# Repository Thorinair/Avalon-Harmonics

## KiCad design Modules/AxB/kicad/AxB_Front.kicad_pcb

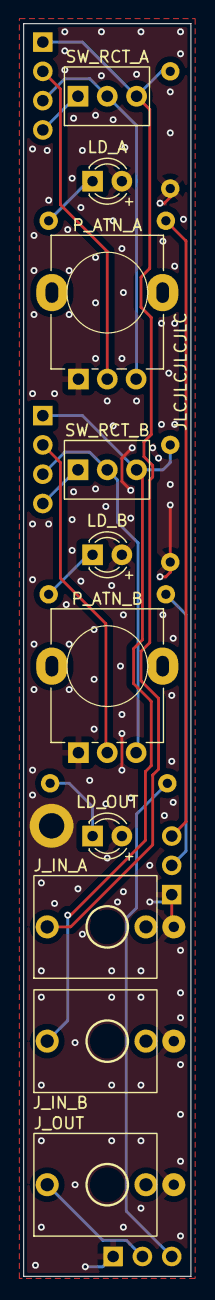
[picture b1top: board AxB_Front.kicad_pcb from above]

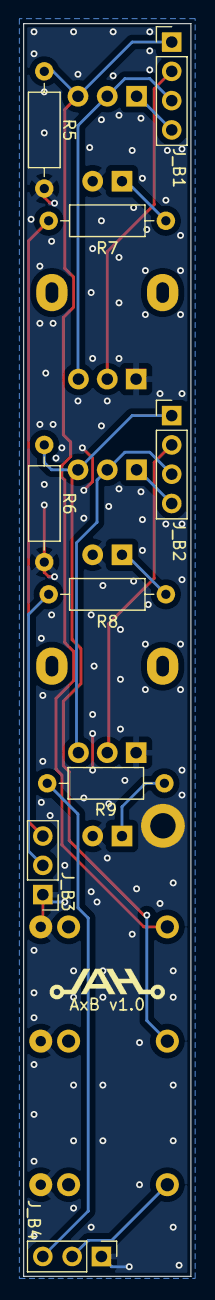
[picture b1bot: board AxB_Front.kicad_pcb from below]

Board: 2 copper layers, 14.5 x 108.6 mm, 19 parts (9 on the bottom side), 16 nets.

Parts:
J_B1, J_B2: Conn_01x04_Female; PinHeader_1x04_P2.54mm_Vertical
J_B3, J_B4: Conn_01x03_Female; PinHeader_1x03_P2.54mm_Vertical
J_IN_A: PJ301M-12
J_IN_B: PJ301M-12
J_OUT: PJ301M-12
LD_A: LED (Bi); LED_D3.0mm_FlatTop
LD_B: LED (Bi); LED_D3.0mm_FlatTop
LD_OUT: LED (Bi); LED_D3.0mm_FlatTop
P_ATN_A: B50k; Potentiometer Alpha RD901F-40-00D
P_ATN_B: B50k; Potentiometer Alpha RD901F-40-00D
R5, R6: 100k; R_Axial_DIN0207_L6.3mm_D2.5mm_P10.16mm_Horizontal
R7, R8, R9: 1k; R_Axial_DIN0207_L6.3mm_D2.5mm_P10.16mm_Horizontal
SW_RCT_A: SW_SPDT; SPDT
SW_RCT_B: SW_SPDT; SPDT

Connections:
GND: J_B3.1, J_B4.1, J_IN_A.GND, J_IN_B.GND, J_OUT.GND, LD_A.2 (A), LD_B.2 (A), LD_OUT.2 (A), P_ATN_A.1, P_ATN_B.1, R5.1, R6.1
unnamed: J_B1.1, J_IN_A.SIG, R5.2, SW_RCT_A.3 (C)
unnamed: J_B1.2, P_ATN_A.2
unnamed: J_B1.3, P_ATN_A.3, SW_RCT_A.2 (B)
unnamed: J_B1.4, SW_RCT_A.1 (A)
unnamed: J_B2.1, J_IN_B.SIG, R6.2, SW_RCT_B.3 (C)
unnamed: J_B2.2, P_ATN_B.2
unnamed: J_B2.3, P_ATN_B.3, SW_RCT_B.2 (B)
unnamed: J_B2.4, SW_RCT_B.1 (A)
unnamed: J_B3.2, R8.2
unnamed: J_B3.3, R7.2
unnamed: J_B4.2, J_OUT.SIG
unnamed: J_B4.3, R9.2
unnamed: LD_A.1 (K), R7.1
unnamed: LD_B.1 (K), R8.1
unnamed: LD_OUT.1 (K), R9.1

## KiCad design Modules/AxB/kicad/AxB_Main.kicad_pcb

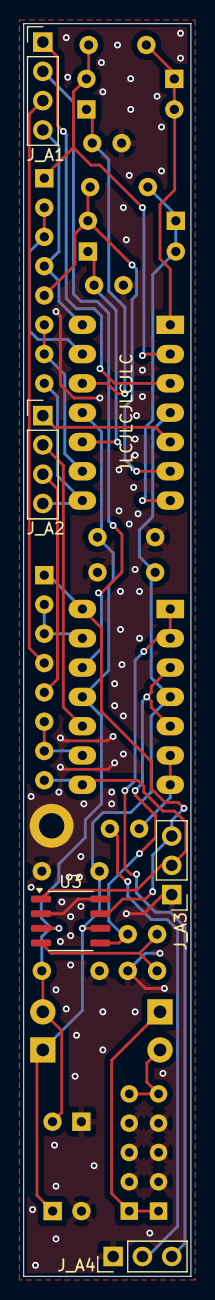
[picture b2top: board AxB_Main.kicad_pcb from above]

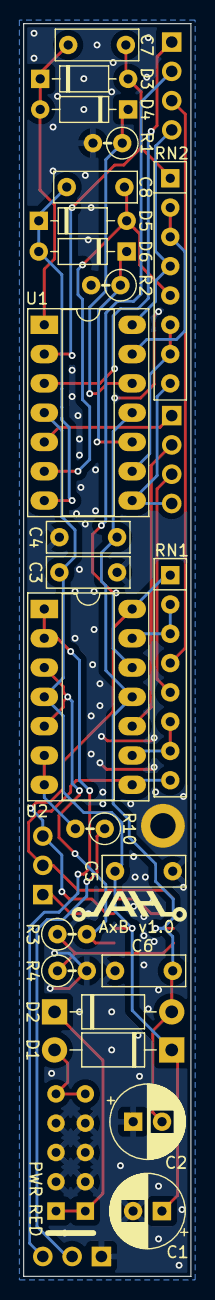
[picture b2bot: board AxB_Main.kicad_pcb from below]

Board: 2 copper layers, 14.5 x 108.6 mm, 29 parts (24 on the bottom side), 30 nets.

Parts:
C1, C2: 47uF; CP_Radial_D6.3mm_P2.50mm
C3, C4, C5, C6: 0.1uF; C_Disc_D7.0mm_W2.5mm_P5.00mm
C7, C8: 47pF; C_Disc_D7.0mm_W2.5mm_P5.00mm
D1, D2: 1N4001; D_DO-41_SOD81_P10.16mm_Horizontal
D3, D4, D5, D6: 1N4148; D_DO-35_SOD27_P7.62mm_Horizontal
J_A1, J_A2: Conn_01x04_Male; PinHeader_1x04_P2.54mm_Vertical
J_A3, J_A4: Conn_01x03_Male; PinHeader_1x03_P2.54mm_Vertical
PWR1: PWR_10_Pin; Eurorack Power 10 Pin
R1, R2: 10k; R_Axial_DIN0207_L6.3mm_D2.5mm_P2.54mm_Vertical
R3: 33k; R_Axial_DIN0207_L6.3mm_D2.5mm_P2.54mm_Vertical
R4: 100k; R_Axial_DIN0207_L6.3mm_D2.5mm_P2.54mm_Vertical
R10: 1k; R_Axial_DIN0207_L6.3mm_D2.5mm_P2.54mm_Vertical
RN1: 100k; R_Array_SIP8
RN2: 10k; R_Array_SIP8
U1, U2: TL074; DIP-14_W7.62mm_Socket_LongPads
U3: AD633JR; SO-8_3.9x4.9mm_P1.27mm

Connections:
+12V: C1.1, C3.1, C5.2, D1.1 (K), U1.4 (V+), U2.4 (V+), U3.6 (+V_{S})
-12V: C2.2, C4.2, C6.2, D2.2 (A), U1.11 (V-), U2.11 (V-), U3.3 (-V_{S})
/AXB: R3.2, U2.3 (+), U2.5 (+), U3.5 (W)
/IN_A: J_A1.1, U1.3 (+)
/IN_B: J_A2.1, U1.5 (+)
/LED_A: J_A3.3, RN1.1 (R1.1), U2.14, U3.7 (X1)
/LED_B: J_A3.2, RN1.8 (R4.2), U2.8, U3.1 (Y1)
/LED_OUT: J_A4.3, U2.1, U2.2 (-)
/OUT: J_A4.2, R10.1
/RECT_A: J_A1.4, RN2.4 (R2.2), U1.14
/RECT_B: J_A2.4, RN2.8 (R4.2), U1.8
GND: C1.2, C2.1, C3.2, C4.1, C5.1, C6.1, J_A3.1, J_A4.1, PWR1.2 (GND), R1.2, R2.2, R4.2, U3.2 (Y2), U3.8 (X2)
unnamed: D1.2 (A), PWR1.1 (+12V)
unnamed: D2.1 (K), PWR1.3 (-12V)
unnamed: C7.1, D3.2 (A), RN2.1 (R1.1), U1.2 (-)
unnamed: C7.2, D3.1 (K), D4.2 (A), U1.1
unnamed: D4.1 (K), R1.1, U1.12 (+)
unnamed: C8.1, D5.2 (A), RN2.5 (R3.1), U1.6 (-)
unnamed: C8.2, D5.1 (K), D6.2 (A), U1.7
unnamed: D6.1 (K), R2.1, U1.10 (+)
unnamed: J_A1.2, U2.12 (+)
unnamed: J_A1.3, RN1.4 (R2.2)
unnamed: J_A2.2, U2.10 (+)
unnamed: J_A2.3, RN1.5 (R3.1)
unnamed: RN1.2 (R1.2), RN1.3 (R2.1), U2.13 (-)
unnamed: RN1.6 (R3.2), RN1.7 (R4.1), U2.9 (-)
unnamed: RN2.2 (R1.2), RN2.3 (R2.1), U1.13 (-)
unnamed: RN2.6 (R3.2), RN2.7 (R4.1), U1.9 (-)
unnamed: R10.2, U2.6 (-), U2.7
unnamed: R3.1, R4.1, U3.4 (Z)

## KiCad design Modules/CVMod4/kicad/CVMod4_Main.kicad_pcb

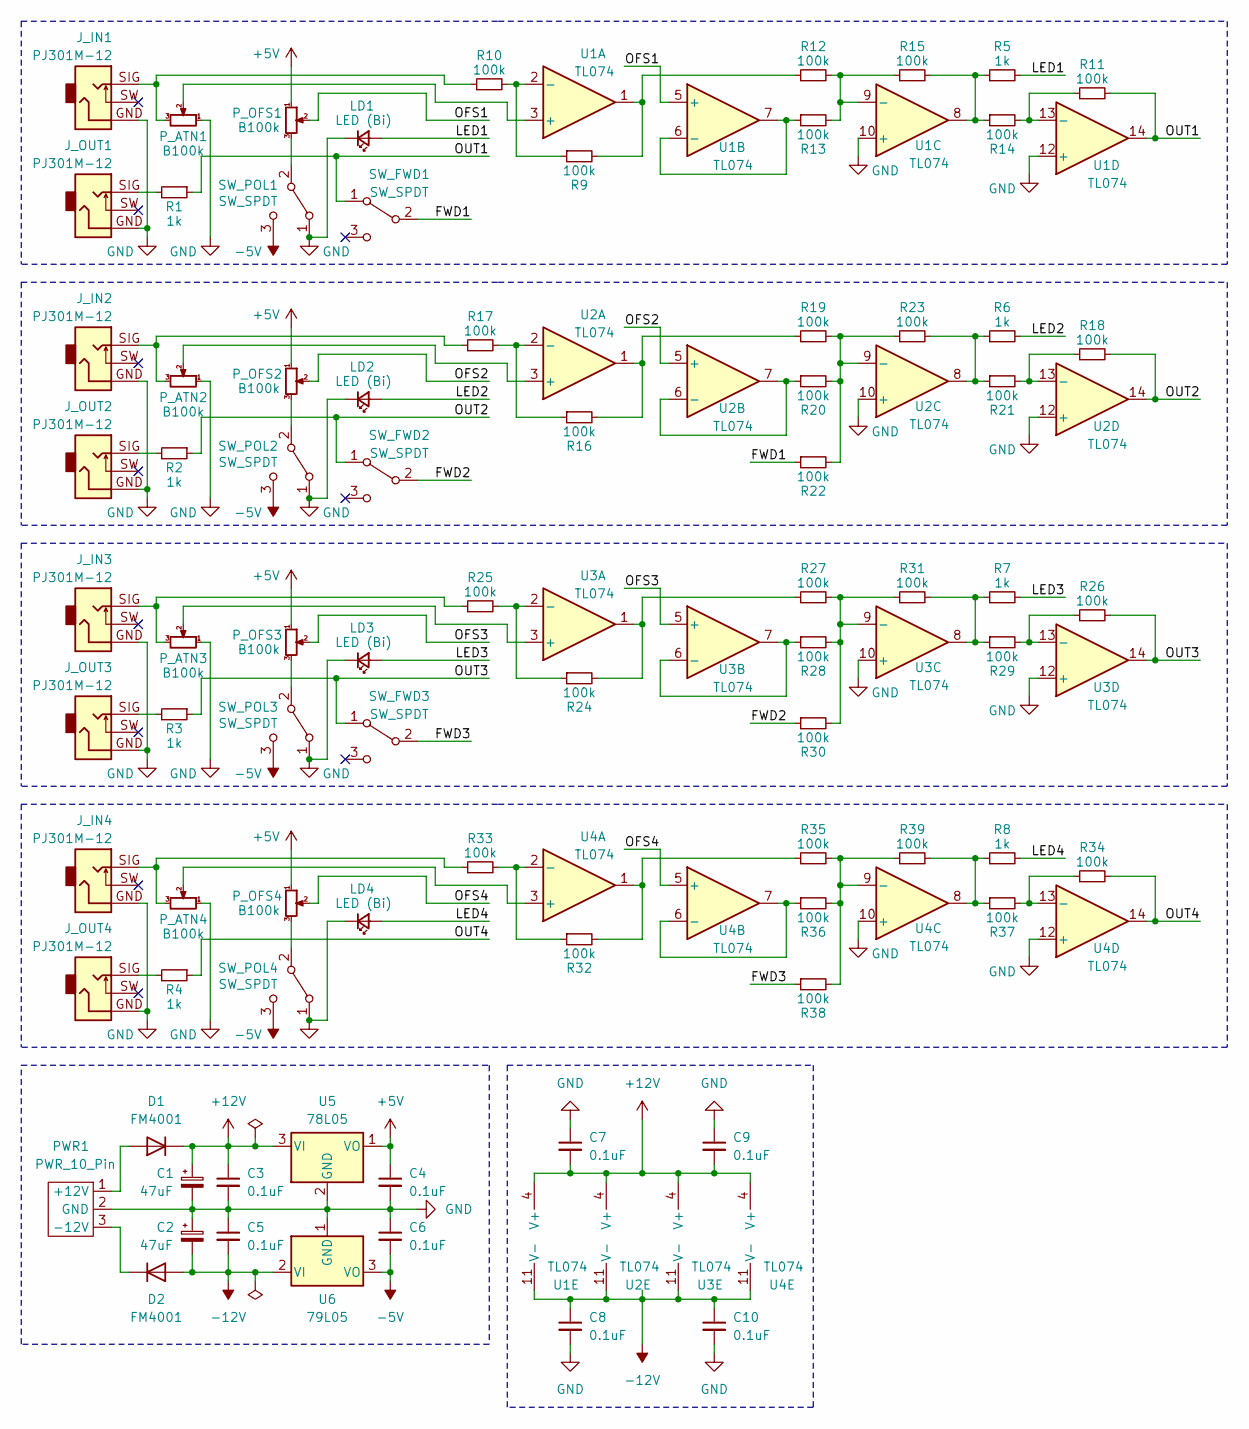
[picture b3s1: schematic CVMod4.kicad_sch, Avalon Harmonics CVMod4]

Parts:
C1, C2: 47uF; CP_Elec_6.3x5.3
C3, C4, C5, C6, C7, C8, C9, C10: 0.1uF; C_0603_1608Metric_Pad1.08x0.95mm_HandSolder
D1, D2: FM4001; D_SOD-123F_AH
J_IN1, J_IN2, J_IN3, J_IN4: PJ301M-12; PJ301M-12 Offset
J_OUT1, J_OUT2, J_OUT3, J_OUT4: PJ301M-12; PJ301M-12 Offset
LD1, LD2, LD3, LD4: LED (Bi); LED_D3.0mm_FlatTop
PWR1: PWR_10_Pin; Eurorack Power 10 Pin
P_ATN1, P_ATN2, P_ATN3, P_ATN4: B100k; Potentiometer Song Huei 9mm Trimmer
P_OFS1, P_OFS2, P_OFS3, P_OFS4: B100k; Potentiometer_Bourns_PTA3043_Single_Slide
R1, R2, R3, R4, R5, R6, R7, R8: 1k; R_0603_1608Metric_Pad0.98x0.95mm_HandSolder
R9, R10, R11, R12, R13, R14, R15, R16, R17, R18, R19, R20, R21, R22, R23, R24, R25, R26, R27, R28, R29, R30, R31, R32, R33, R34, R35, R36, R37, R38, R39: 100k; R_0603_1608Metric_Pad0.98x0.95mm_HandSolder
SW_FWD1, SW_FWD2, SW_FWD3: SW_SPDT; SPDT
SW_POL1, SW_POL2, SW_POL3, SW_POL4: SW_SPDT; SPDT
U1, U2, U3, U4: TL074; SO-14_3.9x8.65mm_P1.27mm_AH
U5: 78L05; SOT-89-3_Handsoldering
U6: 79L05; SOT-89-3_Handsoldering

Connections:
+5V: C4.1, P_OFS1.1, P_OFS2.1, P_OFS3.1, P_OFS4.1, U5.1 (VO)
+12V: C1.1, C3.1, C7.2, C9.2, D1.1 (K), U1.4 (V+), U2.4 (V+), U3.4 (V+), U4.4 (V+), U5.3 (VI)
-5V: C6.2, SW_POL1.3 (C), SW_POL2.3 (C), SW_POL3.3 (C), SW_POL4.3 (C), U6.3 (VO)
-12V: C2.2, C5.2, C8.1, C10.1, D2.2 (A), U1.11 (V-), U2.11 (V-), U3.11 (V-), U4.11 (V-), U6.2 (VI)
/FWD1: R22.1, SW_FWD1.2 (B)
/FWD2: R30.1, SW_FWD2.2 (B)
/FWD3: R38.1, SW_FWD3.2 (B)
/LED1: LD1.2 (A), R5.2
/LED2: LD2.2 (A), R6.2
/LED3: LD3.2 (A), R7.2
/LED4: LD4.2 (A), R8.2
/OFS1: P_OFS1.2, U1.5 (+)
/OFS2: P_OFS2.2, U2.5 (+)
/OFS3: P_OFS3.2, U3.5 (+)
/OFS4: P_OFS4.2, U4.5 (+)
/OUT1: R1.1, R11.2, SW_FWD1.1 (A), U1.14
/OUT2: R2.1, R18.2, SW_FWD2.1 (A), U2.14
/OUT3: R3.1, R26.2, SW_FWD3.1 (A), U3.14
/OUT4: R4.1, R34.2, U4.14
GND: C1.2, C2.1, C3.2, C4.2, C5.1, C6.1, C7.1, C8.2, C9.1, C10.2, J_IN1.GND, J_IN2.GND, J_IN3.GND, J_IN4.GND, J_OUT1.GND, J_OUT2.GND, J_OUT3.GND, J_OUT4.GND, LD1.1 (K), LD2.1 (K), LD3.1 (K), LD4.1 (K), PWR1.2 (GND), P_ATN1.1, P_ATN2.1, P_ATN3.1, P_ATN4.1, SW_POL1.1 (A), SW_POL2.1 (A), SW_POL3.1 (A), SW_POL4.1 (A), U1.10 (+), U1.12 (+), U2.10 (+), U2.12 (+), U3.10 (+), U3.12 (+), U4.10 (+), U4.12 (+), U5.2 (GND), U6.1 (GND)
unnamed: D1.2 (A), PWR1.1 (+12V)
unnamed: D2.1 (K), PWR1.3 (-12V)
unnamed: J_IN1.SIG, P_ATN1.3, R10.1
unnamed: J_IN2.SIG, P_ATN2.3, R17.1
unnamed: J_IN3.SIG, P_ATN3.3, R25.1
unnamed: J_IN4.SIG, P_ATN4.3, R33.1
unnamed: J_OUT1.SIG, R1.2
unnamed: J_OUT2.SIG, R2.2
unnamed: J_OUT3.SIG, R3.2
unnamed: J_OUT4.SIG, R4.2
unnamed: R9.2, R12.1, U1.1
unnamed: R5.1, R14.1, R15.2, U1.8
unnamed: R16.2, R19.1, U2.1
unnamed: R6.1, R21.1, R23.2, U2.8
unnamed: R24.2, R27.1, U3.1
unnamed: R7.1, R29.1, R31.2, U3.8
unnamed: R32.2, R35.1, U4.1
unnamed: R8.1, R37.1, R39.2, U4.8
unnamed: P_OFS1.3, SW_POL1.2 (B)
unnamed: P_OFS2.3, SW_POL2.2 (B)
unnamed: P_OFS3.3, SW_POL3.2 (B)
unnamed: P_OFS4.3, SW_POL4.2 (B)
unnamed: P_ATN1.2, U1.3 (+)
unnamed: R9.1, R10.2, U1.2 (-)
unnamed: R13.1, U1.6 (-), U1.7
unnamed: R12.2, R13.2, R15.1, U1.9 (-)
unnamed: R11.1, R14.2, U1.13 (-)
unnamed: P_ATN2.2, U2.3 (+)
unnamed: R16.1, R17.2, U2.2 (-)
unnamed: R20.1, U2.6 (-), U2.7
unnamed: R19.2, R20.2, R22.2, R23.1, U2.9 (-)
unnamed: R18.1, R21.2, U2.13 (-)
unnamed: P_ATN3.2, U3.3 (+)
unnamed: R24.1, R25.2, U3.2 (-)
unnamed: R28.1, U3.6 (-), U3.7
unnamed: R27.2, R28.2, R30.2, R31.1, U3.9 (-)
unnamed: R26.1, R29.2, U3.13 (-)
unnamed: P_ATN4.2, U4.3 (+)
unnamed: R32.1, R33.2, U4.2 (-)
unnamed: R36.1, U4.6 (-), U4.7
unnamed: R35.2, R36.2, R38.2, R39.1, U4.9 (-)
unnamed: R34.1, R37.2, U4.13 (-)

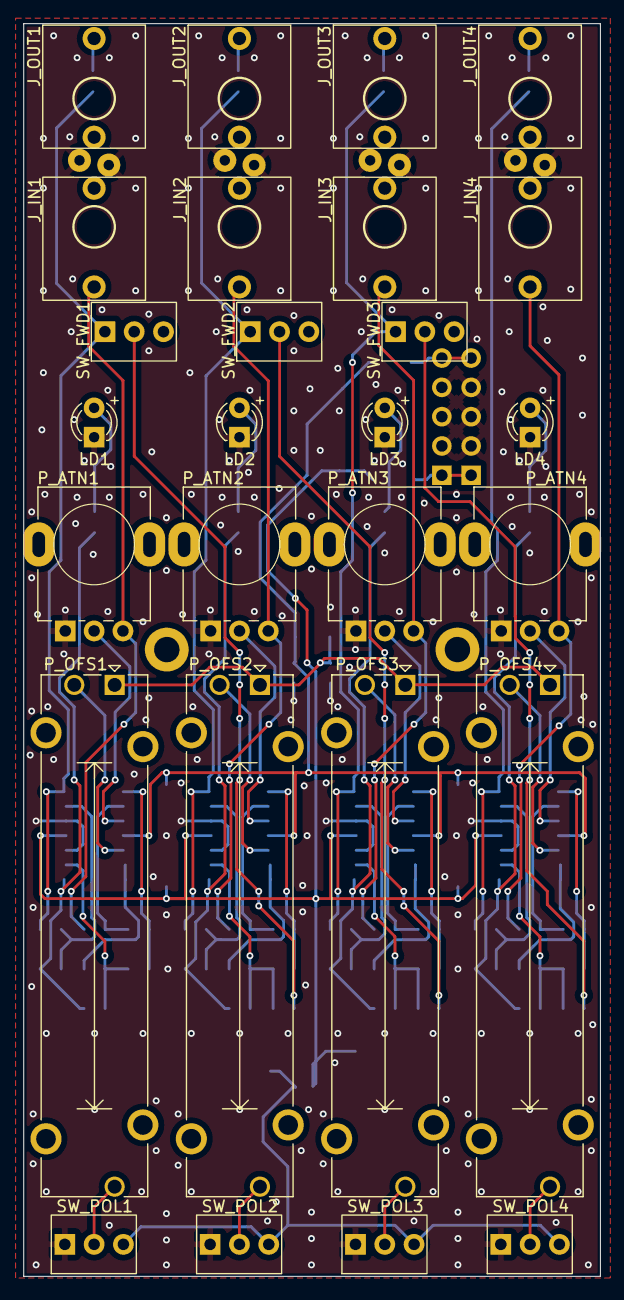
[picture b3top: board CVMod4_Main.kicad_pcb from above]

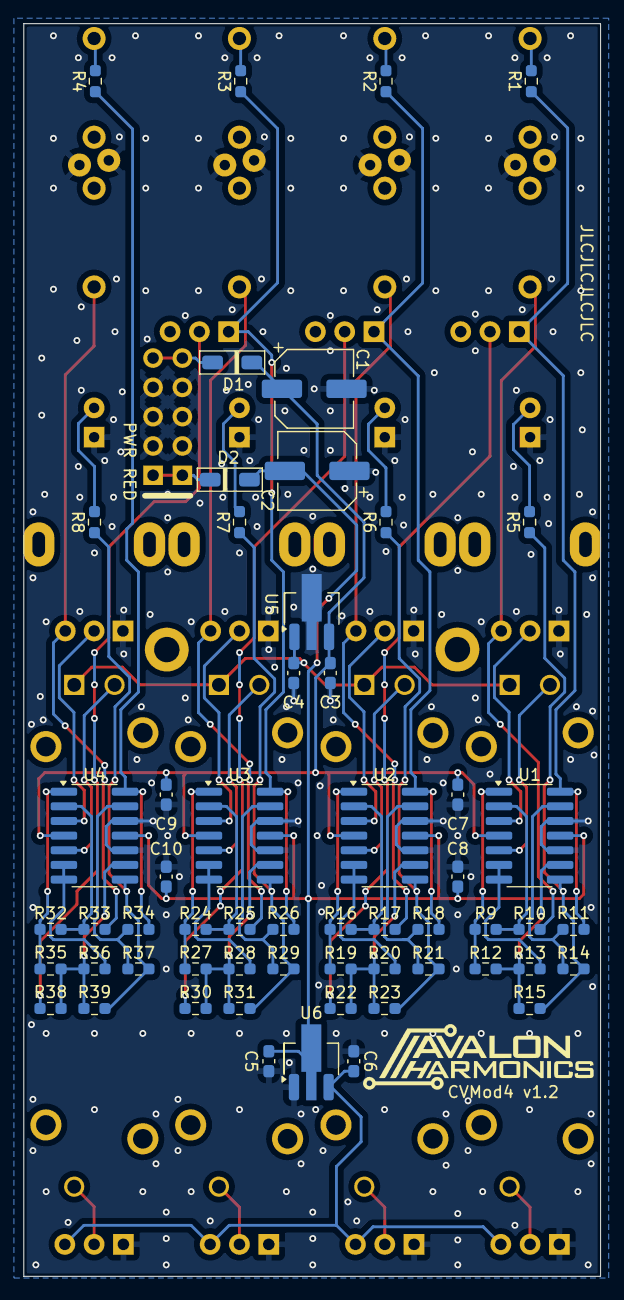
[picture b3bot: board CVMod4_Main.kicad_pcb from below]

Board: 2 copper layers, 50.0 x 108.6 mm, 85 parts (58 on the bottom side), 62 nets.

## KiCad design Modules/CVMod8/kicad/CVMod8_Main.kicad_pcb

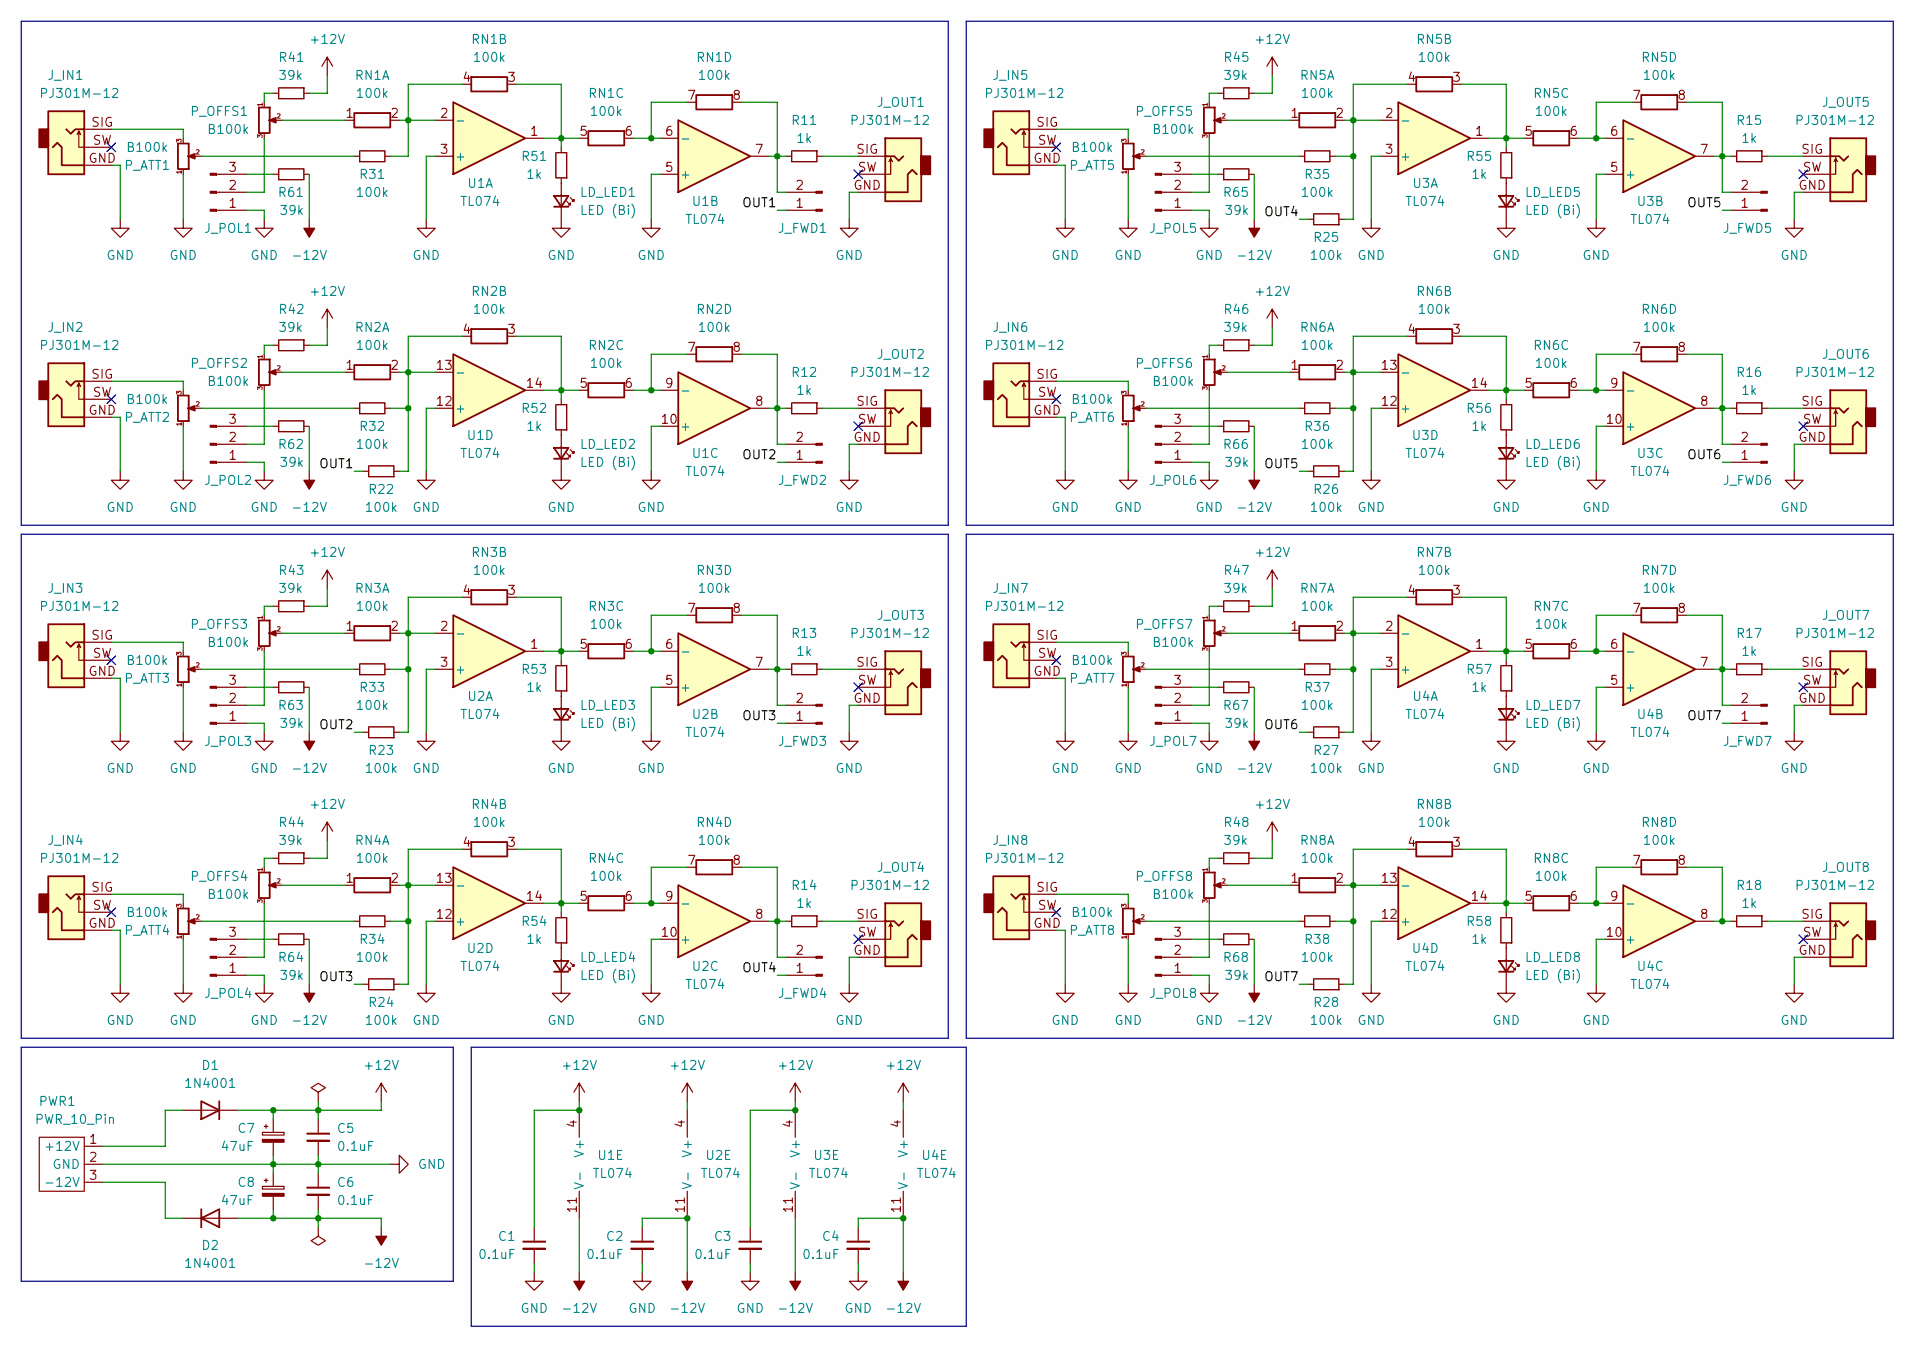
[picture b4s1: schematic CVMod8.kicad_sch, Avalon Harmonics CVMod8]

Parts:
C1, C2, C3, C4, C5: 0.1uF; C_Disc_D7.0mm_W2.5mm_P5.00mm
C6: 0.1uF; C_Disc_D7.5mm_W2.5mm_P5.00mm
C7, C8: 47uF; CP_Radial_D6.3mm_P2.50mm
D1, D2: 1N4001; D_DO-41_SOD81_P10.16mm_Horizontal
J_FWD1, J_FWD2, J_FWD3, J_FWD4, J_FWD5, J_FWD6, J_FWD7: Conn_01x02_Male; PinHeader_1x02_P2.54mm_Vertical
J_IN1, J_IN2, J_IN3, J_IN4, J_IN5, J_IN6, J_IN7, J_IN8: PJ301M-12; PJ301M-12 Offset
J_OUT1, J_OUT2, J_OUT3, J_OUT4, J_OUT5, J_OUT6, J_OUT7, J_OUT8: PJ301M-12; PJ301M-12 Offset
J_POL1, J_POL2, J_POL3, J_POL4, J_POL5, J_POL6, J_POL7, J_POL8: Conn_01x03_Male; PinHeader_1x03_P2.54mm_Vertical
LD_LED1, LD_LED2, LD_LED3, LD_LED4, LD_LED5, LD_LED6, LD_LED7, LD_LED8: LED (Bi); LED_D3.0mm_FlatTop
PWR1: PWR_10_Pin; Eurorack Power 10 Pin
P_ATT1, P_ATT2, P_ATT3, P_ATT4, P_ATT5, P_ATT6, P_ATT7, P_ATT8: B100k; Potentiometer Song Huei 9mm Trimmer
P_OFFS1, P_OFFS2, P_OFFS3, P_OFFS4, P_OFFS5, P_OFFS6, P_OFFS7, P_OFFS8: B100k; Potentiometer_Song_Huei_SL3015N_Single_Slide
R11, R12, R13, R14, R15, R16, R17, R18, R51, R52, R53, R54, R55, R56, R57, R58: 1k; R_Axial_DIN0207_L6.3mm_D2.5mm_P2.54mm_Vertical
R22, R23, R24, R25, R26, R27, R28, R31, R32, R33, R34, R35, R36, R37, R38: 100k; R_Axial_DIN0207_L6.3mm_D2.5mm_P2.54mm_Vertical
R41, R42, R43, R44, R45, R46, R47, R48, R61, R62, R63, R64, R65, R66, R67, R68: 39k; R_Axial_DIN0207_L6.3mm_D2.5mm_P2.54mm_Vertical
RN1, RN2, RN3, RN4, RN5, RN6, RN7, RN8: 100k; R_Array_SIP8
U1, U2, U3, U4: TL074; DIP-14_W7.62mm_Socket_LongPads

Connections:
+12V: C1.1, C3.1, C5.1, C7.1, D1.1 (K), R41.1, R42.1, R43.1, R44.1, R45.1, R46.1, R47.1, R48.1, U1.4 (V+), U2.4 (V+), U3.4 (V+), U4.4 (V+)
-12V: C2.1, C4.1, C6.2, C8.2, D2.2 (A), R61.2, R62.2, R63.2, R64.2, R65.2, R66.2, R67.2, R68.2, U1.11 (V-), U2.11 (V-), U3.11 (V-), U4.11 (V-)
/OUT1: J_FWD1.1, R22.2
/OUT2: J_FWD2.1, R23.2
/OUT3: J_FWD3.1, R24.2
/OUT4: J_FWD4.1, R25.2
/OUT5: J_FWD5.1, R26.2
/OUT6: J_FWD6.1, R27.2
/OUT7: J_FWD7.1, R28.2
GND: C1.2, C2.2, C3.2, C4.2, C5.2, C6.1, C7.2, C8.1, J_IN1.GND, J_IN2.GND, J_IN3.GND, J_IN4.GND, J_IN5.GND, J_IN6.GND, J_IN7.GND, J_IN8.GND, J_OUT1.GND, J_OUT2.GND, J_OUT3.GND, J_OUT4.GND, J_OUT5.GND, J_OUT6.GND, J_OUT7.GND, J_OUT8.GND, J_POL1.1, J_POL2.1, J_POL3.1, J_POL4.1, J_POL5.1, J_POL6.1, J_POL7.1, J_POL8.1, LD_LED1.1 (K), LD_LED2.1 (K), LD_LED3.1 (K), LD_LED4.1 (K), LD_LED5.1 (K), LD_LED6.1 (K), LD_LED7.1 (K), LD_LED8.1 (K), PWR1.2 (GND), P_ATT1.1, P_ATT2.1, P_ATT3.1, P_ATT4.1, P_ATT5.1, P_ATT6.1, P_ATT7.1, P_ATT8.1, U1.3 (+), U1.5 (+), U1.10 (+), U1.12 (+), U2.3 (+), U2.5 (+), U2.10 (+), U2.12 (+), U3.3 (+), U3.5 (+), U3.10 (+), U3.12 (+), U4.3 (+), U4.5 (+), U4.10 (+), U4.12 (+)
unnamed: D1.2 (A), PWR1.1 (+12V)
unnamed: D2.1 (K), PWR1.3 (-12V)
unnamed: J_FWD1.2, R11.2, RN1.8 (R4.2), U1.7
unnamed: J_FWD2.2, R12.2, RN2.8 (R4.2), U1.8
unnamed: J_FWD3.2, R13.2, RN3.8 (R4.2), U2.7
unnamed: J_FWD4.2, R14.2, RN4.8 (R4.2), U2.8
unnamed: J_IN1.SIG, P_ATT1.3
unnamed: J_IN2.SIG, P_ATT2.3
unnamed: J_IN3.SIG, P_ATT3.3
unnamed: J_IN4.SIG, P_ATT4.3
unnamed: J_IN5.SIG, P_ATT5.3
unnamed: J_IN6.SIG, P_ATT6.3
unnamed: J_IN7.SIG, P_ATT7.3
unnamed: J_IN8.SIG, P_ATT8.3
unnamed: J_OUT1.SIG, R11.1
unnamed: J_OUT2.SIG, R12.1
unnamed: J_OUT3.SIG, R13.1
unnamed: J_OUT4.SIG, R14.1
unnamed: J_OUT5.SIG, R15.1
unnamed: J_OUT6.SIG, R16.1
unnamed: J_OUT7.SIG, R17.1
unnamed: J_OUT8.SIG, R18.1
unnamed: J_POL1.2, P_OFFS1.3
unnamed: J_POL1.3, R61.1
unnamed: J_POL2.2, P_OFFS2.3
unnamed: J_POL2.3, R62.1
unnamed: J_POL3.2, P_OFFS3.3
unnamed: J_POL3.3, R63.1
unnamed: J_POL4.2, P_OFFS4.3
unnamed: J_POL4.3, R64.1
unnamed: J_POL5.3, R65.1
unnamed: J_POL6.3, R66.1
unnamed: J_POL7.3, R67.1
unnamed: J_POL8.3, R68.1
unnamed: LD_LED1.2 (A), R51.1
unnamed: LD_LED2.2 (A), R52.1
unnamed: LD_LED3.2 (A), R53.1
unnamed: LD_LED4.2 (A), R54.1
unnamed: LD_LED5.2 (A), R55.1
unnamed: LD_LED6.2 (A), R56.1
unnamed: LD_LED7.2 (A), R57.1
unnamed: LD_LED8.2 (A), R58.1
unnamed: P_ATT1.2, R31.1
unnamed: P_ATT2.2, R32.1
unnamed: P_ATT3.2, R33.1
unnamed: P_ATT4.2, R34.1
unnamed: P_ATT5.2, R35.1
unnamed: P_ATT6.2, R36.1
unnamed: P_ATT7.2, R37.1
unnamed: P_ATT8.2, R38.1
unnamed: P_OFFS1.1, R41.2
unnamed: P_OFFS1.2, RN1.1 (R1.1)
unnamed: P_OFFS2.1, R42.2
unnamed: P_OFFS2.2, RN2.1 (R1.1)
unnamed: P_OFFS3.1, R43.2
unnamed: P_OFFS4.1, R44.2
unnamed: P_OFFS5.1, R45.2
unnamed: P_OFFS5.2, RN5.1 (R1.1)
unnamed: J_POL5.2, P_OFFS5.3
unnamed: P_OFFS6.1, R46.2
unnamed: P_OFFS6.2, RN6.1 (R1.1)
unnamed: J_POL6.2, P_OFFS6.3
unnamed: P_OFFS7.1, R47.2
unnamed: P_OFFS7.2, RN7.1 (R1.1)
unnamed: J_POL7.2, P_OFFS7.3
unnamed: P_OFFS8.1, R48.2
unnamed: P_OFFS8.2, RN8.1 (R1.1)
unnamed: J_POL8.2, P_OFFS8.3
unnamed: R22.1, R32.2, RN2.2 (R1.2), RN2.4 (R2.2), U1.13 (-)
unnamed: R24.1, R34.2, RN4.2 (R1.2), RN4.4 (R2.2), U2.13 (-)
unnamed: R31.2, RN1.2 (R1.2), RN1.4 (R2.2), U1.2 (-)
unnamed: R51.2, RN1.3 (R2.1), RN1.5 (R3.1), U1.1
unnamed: R52.2, RN2.3 (R2.1), RN2.5 (R3.1), U1.14
unnamed: R54.2, RN4.3 (R2.1), RN4.5 (R3.1), U2.14
unnamed: RN1.6 (R3.2), RN1.7 (R4.1), U1.6 (-)
unnamed: RN2.6 (R3.2), RN2.7 (R4.1), U1.9 (-)
unnamed: P_OFFS3.2, RN3.1 (R1.1)
unnamed: P_OFFS4.2, RN4.1 (R1.1)
unnamed: R53.2, RN3.3 (R2.1), RN3.5 (R3.1), U2.1
unnamed: R23.1, R33.2, RN3.2 (R1.2), RN3.4 (R2.2), U2.2 (-)
unnamed: RN3.6 (R3.2), RN3.7 (R4.1), U2.6 (-)
unnamed: RN4.6 (R3.2), RN4.7 (R4.1), U2.9 (-)
unnamed: R55.2, RN5.3 (R2.1), RN5.5 (R3.1), U3.1
unnamed: R25.1, R35.2, RN5.2 (R1.2), RN5.4 (R2.2), U3.2 (-)
unnamed: RN5.6 (R3.2), RN5.7 (R4.1), U3.6 (-)
unnamed: J_FWD5.2, R15.2, RN5.8 (R4.2), U3.7
unnamed: J_FWD6.2, R16.2, RN6.8 (R4.2), U3.8
unnamed: RN6.6 (R3.2), RN6.7 (R4.1), U3.9 (-)
unnamed: R26.1, R36.2, RN6.2 (R1.2), RN6.4 (R2.2), U3.13 (-)
unnamed: R56.2, RN6.3 (R2.1), RN6.5 (R3.1), U3.14
unnamed: R57.2, RN7.3 (R2.1), RN7.5 (R3.1), U4.1
unnamed: R27.1, R37.2, RN7.2 (R1.2), RN7.4 (R2.2), U4.2 (-)
unnamed: RN7.6 (R3.2), RN7.7 (R4.1), U4.6 (-)
unnamed: J_FWD7.2, R17.2, RN7.8 (R4.2), U4.7
unnamed: R18.2, RN8.8 (R4.2), U4.8
unnamed: RN8.6 (R3.2), RN8.7 (R4.1), U4.9 (-)
unnamed: R28.1, R38.2, RN8.2 (R1.2), RN8.4 (R2.2), U4.13 (-)
unnamed: R58.2, RN8.3 (R2.1), RN8.5 (R3.1), U4.14

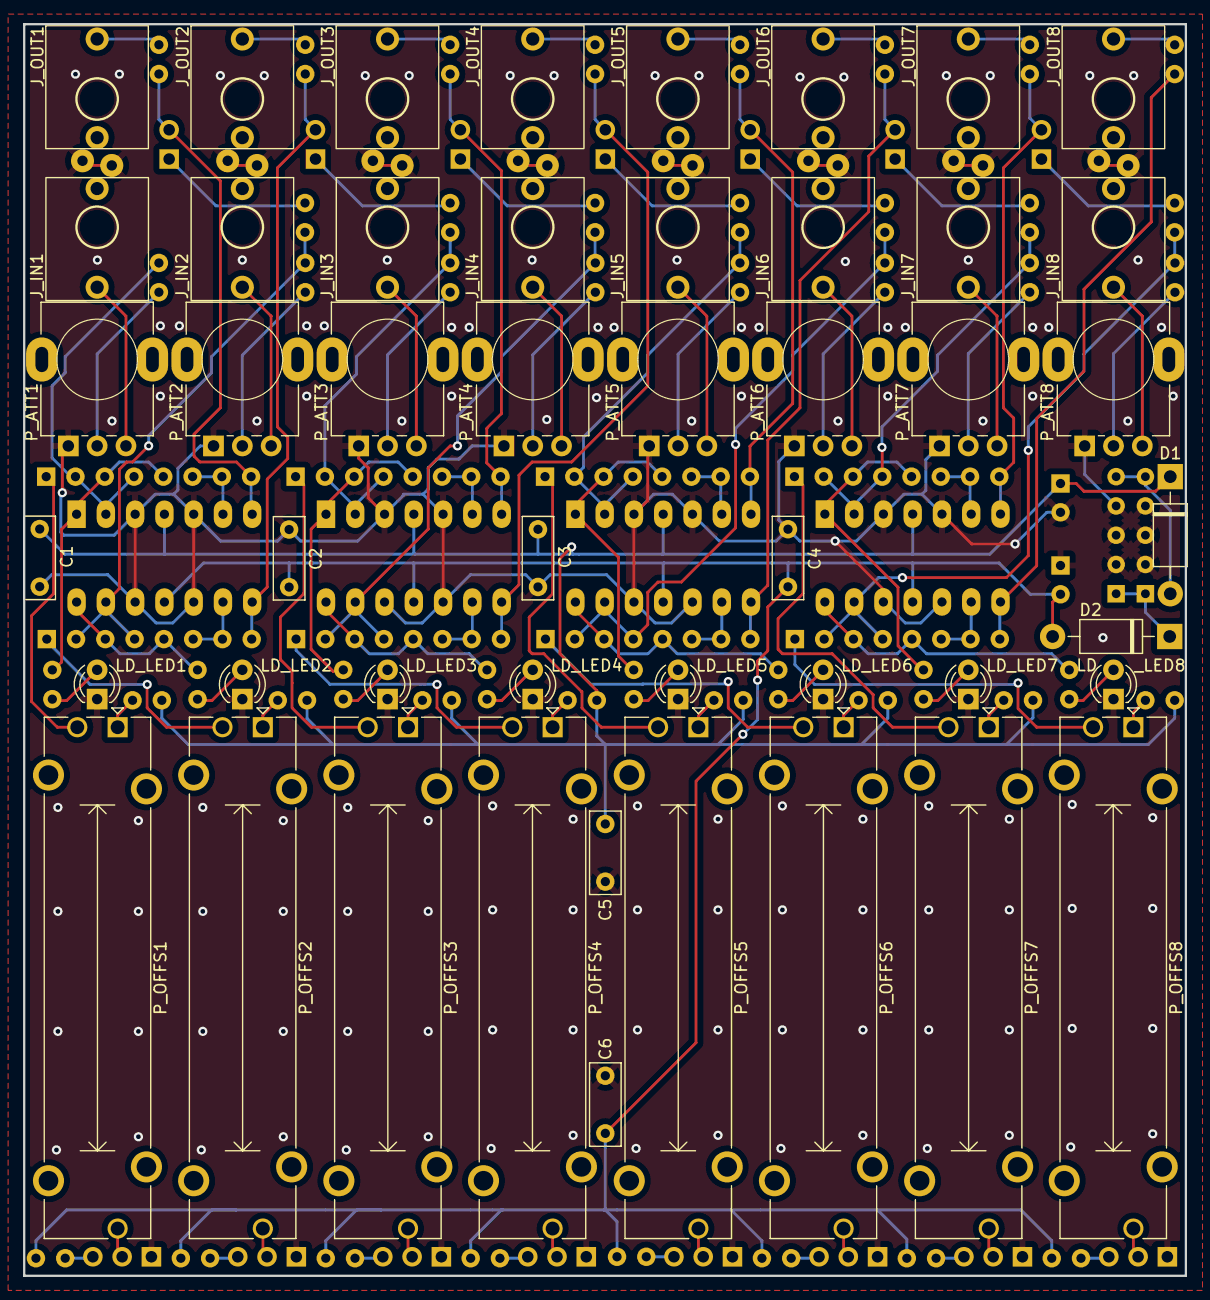
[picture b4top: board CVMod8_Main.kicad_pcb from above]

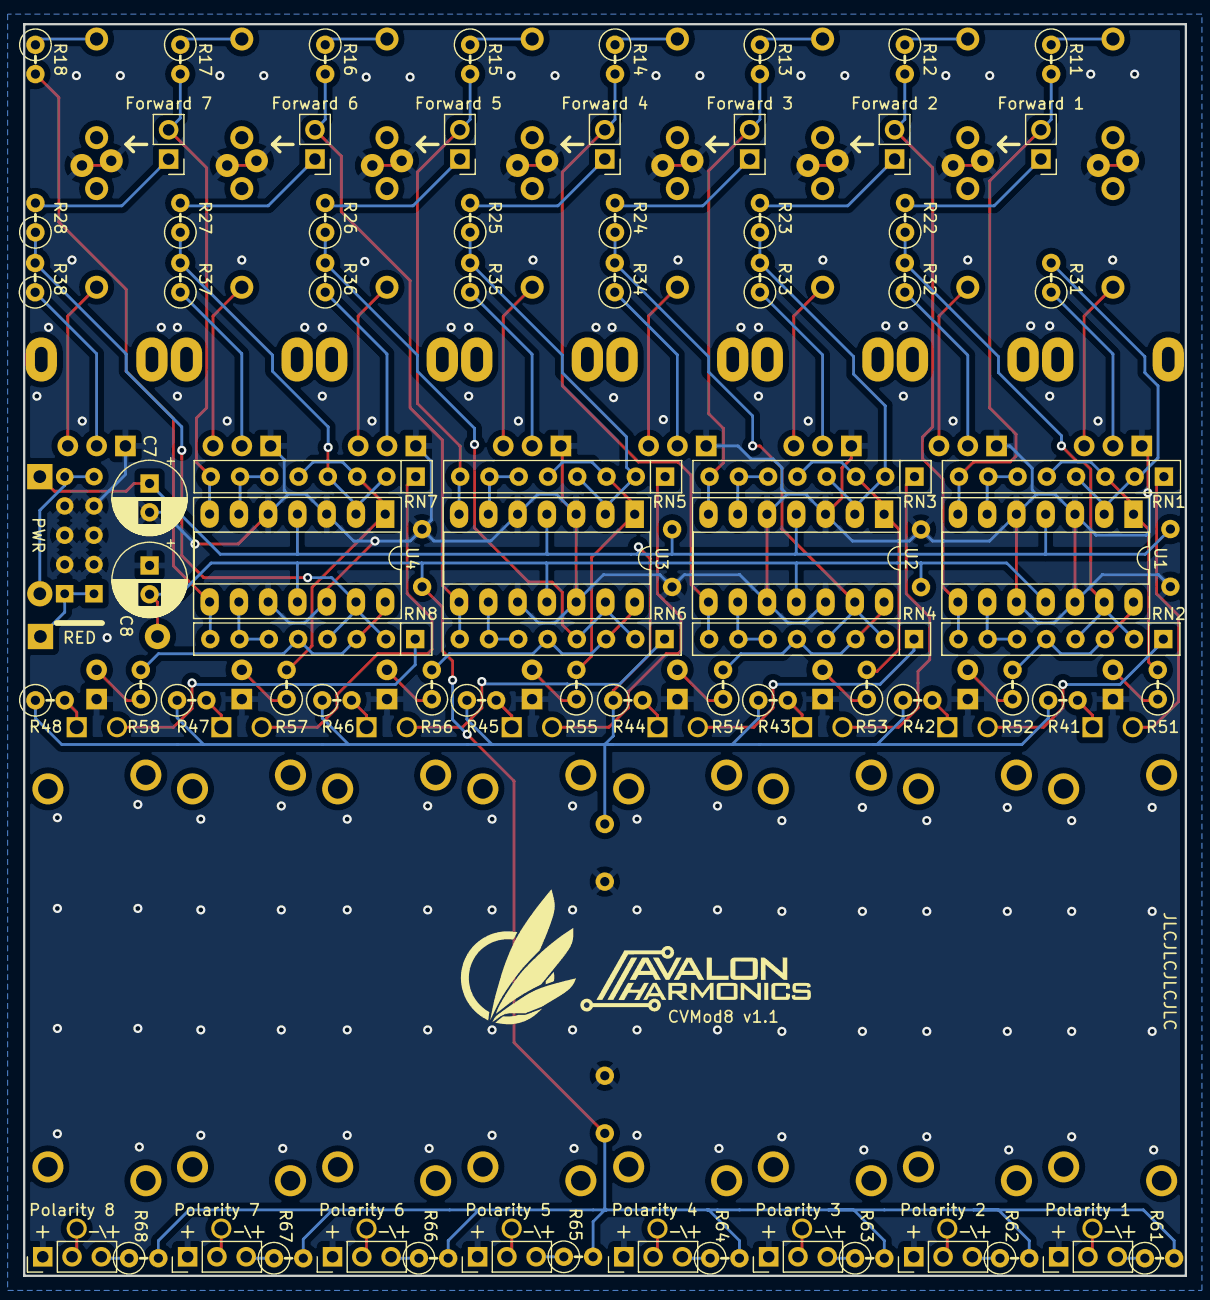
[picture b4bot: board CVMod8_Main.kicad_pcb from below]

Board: 2 copper layers, 100.8 x 108.6 mm, 125 parts (77 on the bottom side), 108 nets.
